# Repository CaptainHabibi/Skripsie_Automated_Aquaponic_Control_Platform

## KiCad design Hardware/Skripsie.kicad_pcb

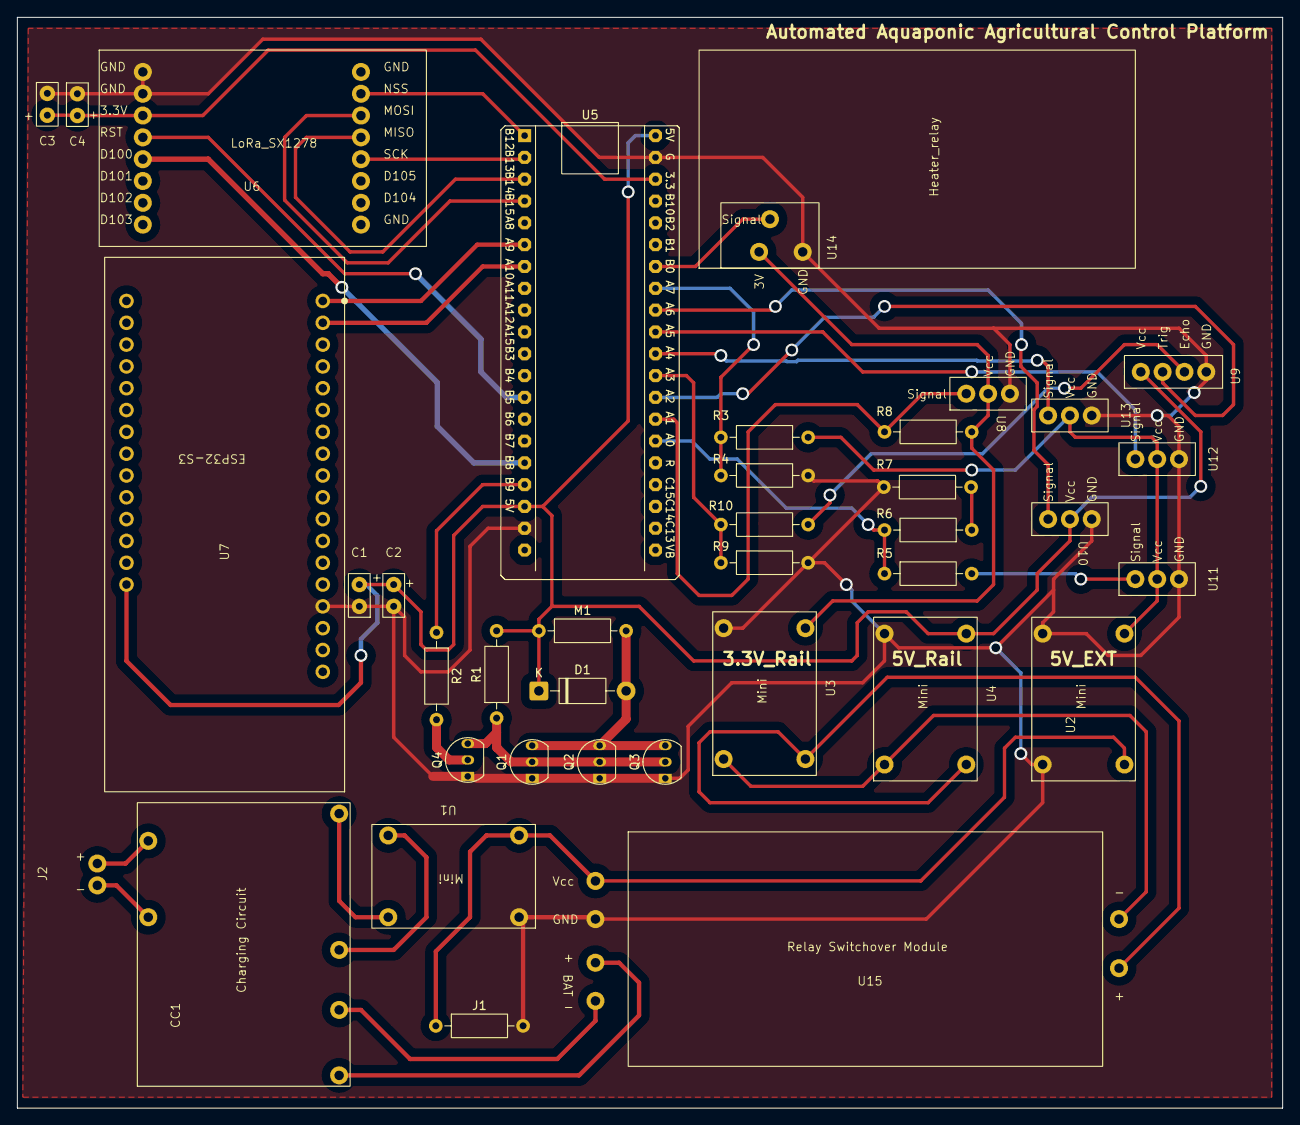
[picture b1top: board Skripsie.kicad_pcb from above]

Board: 2 copper layers, 147.3 x 127.0 mm, 38 parts (0 on the bottom side), 38 nets.

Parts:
C1, C3: 100n; Capacitor_Lab
C2, C4: 100u; Capacitor_Lab
CC1: Charging_Circuit
D1: 1N4007; D_DO-41_SOD81_P10.16mm_Horizontal
J1: Barrel_Jack; R_Axial_DIN0207_L6.3mm_D2.5mm_P10.16mm_Horizontal
J2: Battery Connector Pins; BattConnector
M1: Motor_DC; R_Axial_DIN0207_L6.3mm_D2.5mm_P10.16mm_Horizontal
Q1, Q2, Q3: 2N7000; TO-92_Inline
Q4: 2N3904; TO-92_Inline
R1: 680; R_Axial_DIN0207_L6.3mm_D2.5mm_P10.16mm_Horizontal
R2, R10: 1k; R_Axial_DIN0207_L6.3mm_D2.5mm_P10.16mm_Horizontal
R3, R5: 12k; R_Axial_DIN0207_L6.3mm_D2.5mm_P10.16mm_Horizontal
R4: 22k; R_Axial_DIN0207_L6.3mm_D2.5mm_P10.16mm_Horizontal
R6: 30k; R_Axial_DIN0207_L6.3mm_D2.5mm_P10.16mm_Horizontal
R7: 3.3k; R_Axial_DIN0207_L6.3mm_D2.5mm_P10.16mm_Horizontal
R8: 4.7k; R_Axial_DIN0207_L6.3mm_D2.5mm_P10.16mm_Horizontal
R9: 2k; R_Axial_DIN0207_L6.3mm_D2.5mm_P10.16mm_Horizontal
U1, U2, U3, U4: VoltageRegulator_ZX_Mini_360
U5: STM32F411 BlackPill; STM32F411_Black_Pill
U6: LoRa_SX1278
U7: FireBeetle2_ESP32S3
U8, U10, U11, U12, U13: Sensor_Interface_3Pin
U9: UltraSonic_HCSR04
U14: Heater_Relay_Footprint
U15: Switchover_Relay

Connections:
3.3V_Rail: R8.2, U3.4 (OUT+), U8.2 (VDD), U14.1 (3V)
5V_EXT: R3.1, U2.4 (OUT+), U11.2 (Vcc), U12.2 (Vcc), U13.2 (Vcc)
5V_Rail: C1.1, C2.1, D1.1 (K), M1.1 (+), R1.2, U4.4 (OUT+), U5.18 (5V), U5.40 (5V), U7.19 (VCC), U9.4 (Vcc), U10.2 (Vcc)
+12V: J1.1, U1.2 (IN+), U2.2 (IN+), U15.1 (Vcc)
/3.3V_STM: C3.1, C4.1, U5.38 (3.3V), U6.3 (3.3V)
/ECSensor: U5.31 (A5), U12.3 (Signal)
/Echo: R9.1, R10.2, U5.29 (A3)
/HeaterRelay: U5.34 (B0), U14.2 (Signal)
/LoRa_CS: U5.1 (B12), U6.10 (NSS)
/LoRa_D100: U5.16 (B8), U6.5 (D100)
/LoRa_Rst: U5.13 (B5), U6.4 (RST)
/PHSensor: U5.30 (A4), U13.3 (Signal)
/PowerCheck: R3.2, R4.1, U5.33 (A7)
/Pump_PWM: R2.1, U5.17 (B9)
/SPI2_MISO: U5.3 (B14), U6.12 (MISO)
/SPI2_MOSI: U5.4 (B15), U6.11 (MOSI)
/SPI2_SCK: U5.2 (B13), U6.13 (SCK)
/Servo_PWM: U5.32 (A6), U10.3 (Signal)
/TempSensorPin: R8.1, U5.27 (A1), U8.3 (Signal)
/Trig: U5.28 (A2), U9.3 (Trig)
/Turbidity: R5.1, R6.2, U5.26 (A0)
/USART1_RX: U5.7 (A10), U7.2 (TX)
/USART1_TX: U5.6 (A9), U7.1 (RX)
GND: C1.2, C2.2, C3.2, C4.2, J1.2, Q1.1 (S), Q2.1 (S), Q3.1 (S), Q4.1 (E), R4.2, R7.2, R9.2, U1.1 (IN-), U2.1 (IN-), U2.3 (OUT-), U3.3 (OUT-), U4.3 (OUT-), U5.19 (G), U5.39 (G), U6.1 (GND), U6.2 (GND), U7.15 (GND), U8.1 (GND), U9.1 (GND), U10.1 (GND), U11.1 (GND), U12.1 (GND), U13.1 (GND), U14.3 (GND), U15.2 (GND)
unnamed: CC1.3 (BAT+), J2.2
unnamed: CC1.4 (BAT-), J2.1
unnamed: CC1.5 (IN+), U1.4 (OUT+)
unnamed: CC1.6 (IN-), U1.3 (OUT-)
unnamed: CC1.1 (Vout+), U15.3 (BAT+)
unnamed: CC1.2 (Vout-), U15.4 (BAT-)
unnamed: D1.2 (A), M1.2 (-), Q1.3 (D), Q2.3 (D), Q3.3 (D)
unnamed: Q1.2 (G), Q2.2 (G), Q3.2 (G), Q4.3 (C), R1.1
unnamed: Q4.2 (B), R2.2
unnamed: R6.1, R7.1
unnamed: R10.1, U9.2 (Echo)
unnamed: R5.2, U11.3 (Signal)
unnamed: U3.2 (IN+), U4.2 (IN+), U15.5 (OUT+)
unnamed: U3.1 (IN-), U4.1 (IN-), U15.6 (OUT-)

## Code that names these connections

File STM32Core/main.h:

/* USER CODE BEGIN Header */
/**
  ******************************************************************************
  * @file           : main.h
  * @brief          : Header for main.c file.
  *                   This file contains the common defines of the application.
  ******************************************************************************
  * @attention
  *
  * Copyright (c) 2026 STMicroelectronics.
  * All rights reserved.
  *
  * This software is licensed under terms that can be found in the LICENSE file
  * in the root directory of this software component.
  * If no LICENSE file comes with this software, it is provided AS-IS.
  *
  ******************************************************************************
  */
/* USER CODE END Header */

/* Define to prevent recursive inclusion -------------------------------------*/
#ifndef __MAIN_H
#define __MAIN_H

#ifdef __cplusplus
extern "C" {
#endif

/* Includes ------------------------------------------------------------------*/
#include "stm32f4xx_hal.h"

/* Private includes ----------------------------------------------------------*/
/* USER CODE BEGIN Includes */

/* USER CODE END Includes */

/* Exported types ------------------------------------------------------------*/
/* USER CODE BEGIN ET */
typedef enum {
    SENSOR_TYPE_TEMP = 0,
    SENSOR_TYPE_WATER_LVL,
    SENSOR_TYPE_TURBIDITY,
    SENSOR_TYPE_PH,
    SENSOR_TYPE_EC
} SensorType_t;

typedef struct {
    SensorType_t type;
    float        value;
    uint32_t     timestamp;
} SensorMsg_t;

typedef struct {
    float temp_c;
    float water_level_cm;
    float turbidity_ntu;
    float ph_val;
    float ec_val;
} SystemTelemetry_t;
/* USER CODE END ET */

/* Exported constants --------------------------------------------------------*/
/* USER CODE BEGIN EC */

/* USER CODE END EC */

/* Exported macro ------------------------------------------------------------*/
/* USER CODE BEGIN EM */

/* USER CODE END EM */

/* Exported functions prototypes ---------------------------------------------*/
void Error_Handler(void);

/* USER CODE BEGIN EFP */

/* USER CODE END EFP */

/* Private defines -----------------------------------------------------------*/
#define ledPin_Pin GPIO_PIN_13
#define ledPin_GPIO_Port GPIOC
#define Turbidity_Pin GPIO_PIN_0
#define Turbidity_GPIO_Port GPIOA
#define TempSensorPin_Pin GPIO_PIN_1
#define TempSensorPin_GPIO_Port GPIOA
#define Trig_Pin GPIO_PIN_2
#define Trig_GPIO_Port GPIOA
#define Echo_Pin GPIO_PIN_3
#define Echo_GPIO_Port GPIOA
#define PHSensor_Pin GPIO_PIN_4
#define PHSensor_GPIO_Port GPIOA
#define ECSensor_Pin GPIO_PIN_5
#define ECSensor_GPIO_Port GPIOA
#define Servo_PWM_Pin GPIO_PIN_6
#define Servo_PWM_GPIO_Port GPIOA
#define PowerCheck_Pin GPIO_PIN_7
#define PowerCheck_GPIO_Port GPIOA
#define HeaterRelay_Pin GPIO_PIN_0
#define HeaterRelay_GPIO_Port GPIOB
#define LoRa_CS_Pin GPIO_PIN_12
#define LoRa_CS_GPIO_Port GPIOB
#define LoRa_Rst_Pin GPIO_PIN_5
#define LoRa_Rst_GPIO_Port GPIOB
#define LoRa_D100_Pin GPIO_PIN_8
#define LoRa_D100_GPIO_Port GPIOB

/* USER CODE BEGIN Private defines */

/* USER CODE END Private defines */

#ifdef __cplusplus
}
#endif

#endif /* __MAIN_H */

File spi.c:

/* USER CODE BEGIN Header */
/**
  ******************************************************************************
  * @file    spi.c
  * @brief   This file provides code for the configuration
  *          of the SPI instances.
  ******************************************************************************
  * @attention
  *
  * Copyright (c) 2026 STMicroelectronics.
  * All rights reserved.
  *
  * This software is licensed under terms that can be found in the LICENSE file
  * in the root directory of this software component.
  * If no LICENSE file comes with this software, it is provided AS-IS.
  *
  ******************************************************************************
  */
/* USER CODE END Header */
/* Includes ------------------------------------------------------------------*/
#include "spi.h"

/* USER CODE BEGIN 0 */

/* USER CODE END 0 */

SPI_HandleTypeDef hspi2;

/* SPI2 init function */
void MX_SPI2_Init(void)
{

  /* USER CODE BEGIN SPI2_Init 0 */

  /* USER CODE END SPI2_Init 0 */

  /* USER CODE BEGIN SPI2_Init 1 */

  /* USER CODE END SPI2_Init 1 */
  hspi2.Instance = SPI2;
  hspi2.Init.Mode = SPI_MODE_MASTER;
  hspi2.Init.Direction = SPI_DIRECTION_2LINES;
  hspi2.Init.DataSize = SPI_DATASIZE_8BIT;
  hspi2.Init.CLKPolarity = SPI_POLARITY_LOW;
  hspi2.Init.CLKPhase = SPI_PHASE_1EDGE;
  hspi2.Init.NSS = SPI_NSS_SOFT;
  hspi2.Init.BaudRatePrescaler = SPI_BAUDRATEPRESCALER_16;
  hspi2.Init.FirstBit = SPI_FIRSTBIT_MSB;
  hspi2.Init.TIMode = SPI_TIMODE_DISABLE;
  hspi2.Init.CRCCalculation = SPI_CRCCALCULATION_DISABLE;
  hspi2.Init.CRCPolynomial = 10;
  if (HAL_SPI_Init(&hspi2) != HAL_OK)
  {
    Error_Handler();
  }
  /* USER CODE BEGIN SPI2_Init 2 */

  /* USER CODE END SPI2_Init 2 */

}

void HAL_SPI_MspInit(SPI_HandleTypeDef* spiHandle)
{

  GPIO_InitTypeDef GPIO_InitStruct = {0};
  if(spiHandle->Instance==SPI2)
  {
  /* USER CODE BEGIN SPI2_MspInit 0 */

  /* USER CODE END SPI2_MspInit 0 */
    /* SPI2 clock enable */
    __HAL_RCC_SPI2_CLK_ENABLE();

    __HAL_RCC_GPIOB_CLK_ENABLE();
    /**SPI2 GPIO Configuration
    PB13     ------> SPI2_SCK
    PB14     ------> SPI2_MISO
    PB15     ------> SPI2_MOSI
    */
    GPIO_InitStruct.Pin = GPIO_PIN_13|GPIO_PIN_14|GPIO_PIN_15;
    GPIO_InitStruct.Mode = GPIO_MODE_AF_PP;
    GPIO_InitStruct.Pull = GPIO_NOPULL;
    GPIO_InitStruct.Speed = GPIO_SPEED_FREQ_VERY_HIGH;
    GPIO_InitStruct.Alternate = GPIO_AF5_SPI2;
    HAL_GPIO_Init(GPIOB, &GPIO_InitStruct);

  /* USER CODE BEGIN SPI2_MspInit 1 */

  /* USER CODE END SPI2_MspInit 1 */
  }
}

void HAL_SPI_MspDeInit(SPI_HandleTypeDef* spiHandle)
{

  if(spiHandle->Instance==SPI2)
  {
  /* USER CODE BEGIN SPI2_MspDeInit 0 */

  /* USER CODE END SPI2_MspDeInit 0 */
    /* Peripheral clock disable */
    __HAL_RCC_SPI2_CLK_DISABLE();

    /**SPI2 GPIO Configuration
    PB13     ------> SPI2_SCK
    PB14     ------> SPI2_MISO
    PB15     ------> SPI2_MOSI
    */
    HAL_GPIO_DeInit(GPIOB, GPIO_PIN_13|GPIO_PIN_14|GPIO_PIN_15);

  /* USER CODE BEGIN SPI2_MspDeInit 1 */

  /* USER CODE END SPI2_MspDeInit 1 */
  }
}

/* USER CODE BEGIN 1 */

/* USER CODE END 1 */
